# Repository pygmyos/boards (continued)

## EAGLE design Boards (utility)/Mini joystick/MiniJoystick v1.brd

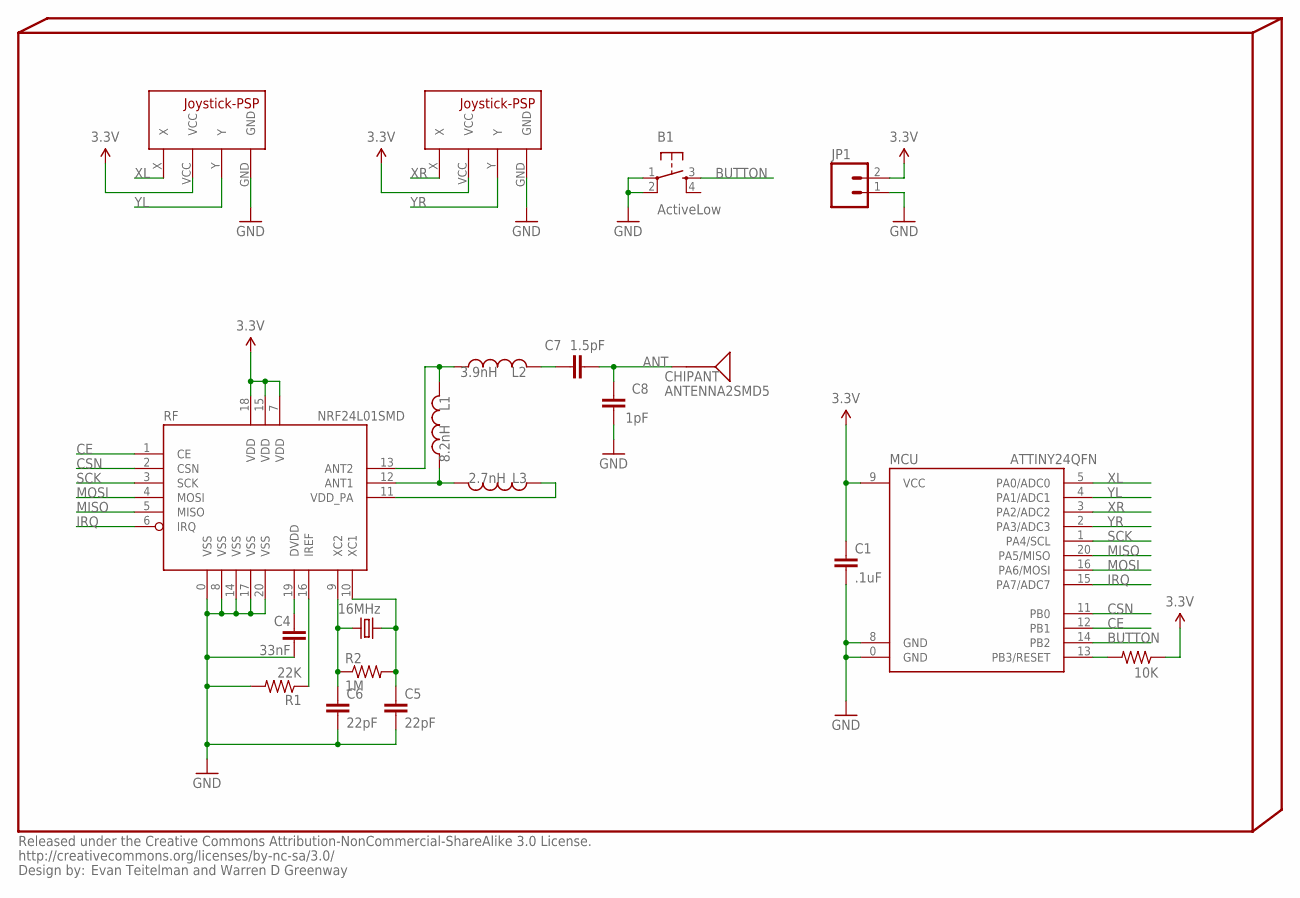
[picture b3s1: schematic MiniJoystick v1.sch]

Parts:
B1: ActiveLow; TACTILE_SWITCH_SMD
C1: .1uF; 0402-CAP
C4: 33nF; 0402-CAP
C5, C6: 22pF; 0402-CAP
C7: 1.5pF; 0402-CAP
C8: 1pF; 0402-CAP
CHIPANT: ANTENNA2SMD5; ANTENNA-CHIP5
INFO4: Evan Teitelman and Warren D Greenway; %CC-NC-SA
JOYSTICK_LEFT: JOYSTICK-PSP1000NOHOLES; JOYSTICK-PSP1000NH_
JOYSTICK_RIGHT: JOYSTICK-PSP1000NOHOLES; JOYSTICK-PSP1000NH_
JP1: M02-JST-2MM-SMT; JST-2-SMD
L1: 8.2nH; C0402
L2: 3.9nH; C0402
L3: 2.7nH; C0402
MCU: ATTINY24QFN; QFN20
R1: 22K; 0603-RES
R2: 1M; 0603-RES
R3: 10K; 0402-RES
RF: NRF24L01SMD; QFN20
Y1: 16MHz; CRYSTAL-SMD-5X3

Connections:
3.3V: C1.1, JOYSTICK_LEFT.VCC, JOYSTICK_RIGHT.VCC, JP1.2, MCU.9 (VCC), R3.1, RF.7 (VDD), RF.15 (VDD), RF.18 (VDD)
ANT: C7.2, C8.2, CHIPANT.FEED
ANT1: L1.1, L3.2, RF.12 (ANT1)
ANT2: L1.2, L2.1, RF.13 (ANT2)
BUTTON: B1.3, MCU.14 (PB2)
CE: MCU.12 (PB1), RF.1 (CE)
CSN: MCU.11 (PB0), RF.2 (CSN)
DVDD: C4.1, RF.19 (DVDD)
GND: B1.1, B1.2, C1.2, C4.2, C5.2, C6.2, C8.1, JOYSTICK_LEFT.GND, JOYSTICK_RIGHT.GND, JP1.1, MCU.0 (GND), MCU.8 (GND), R1.2, RF.0 (VSS), RF.8 (VSS), RF.14 (VSS), RF.17 (VSS), RF.20 (VSS)
IREF: R1.1, RF.16 (IREF)
IRQ: MCU.15 (PA7/ADC7), RF.6 (IRQ)
MISO: MCU.20 (PA5/MISO), RF.5 (MISO)
MOSI: MCU.16 (PA6/MOSI), RF.4 (MOSI)
unnamed: C7.1, L2.2
RESET: MCU.13 (PB3/RESET), R3.2
SCK: MCU.1 (PA4/SCL), RF.3 (SCK)
VDD_PA: L3.1, RF.11 (VDD_PA)
XC1: C5.1, R2.2, RF.10 (XC1), Y1.3 (2)
XC2: C6.1, R2.1, RF.9 (XC2), Y1.1
XL: JOYSTICK_LEFT.X, MCU.5 (PA0/ADC0)
XR: JOYSTICK_RIGHT.X, MCU.3 (PA2/ADC2)
YL: JOYSTICK_LEFT.Y, MCU.4 (PA1/ADC1)
YR: JOYSTICK_RIGHT.Y, MCU.2 (PA3/ADC3)

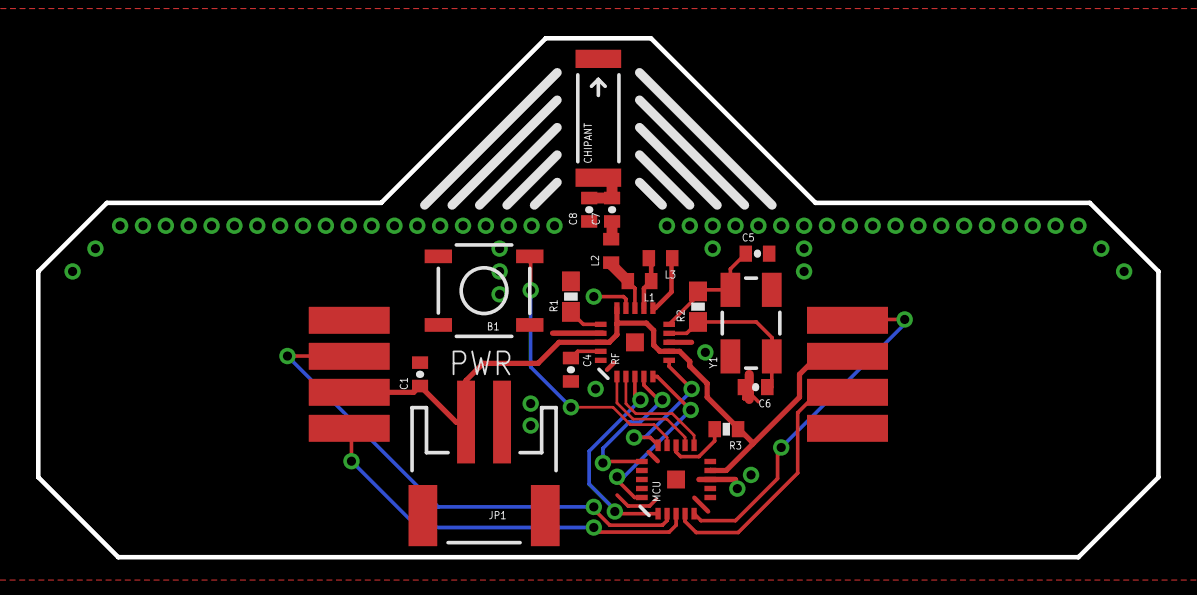
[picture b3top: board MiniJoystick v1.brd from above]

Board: 2 copper layers, 62.2 x 28.8 mm, 21 parts (0 on the bottom side), 23 nets.

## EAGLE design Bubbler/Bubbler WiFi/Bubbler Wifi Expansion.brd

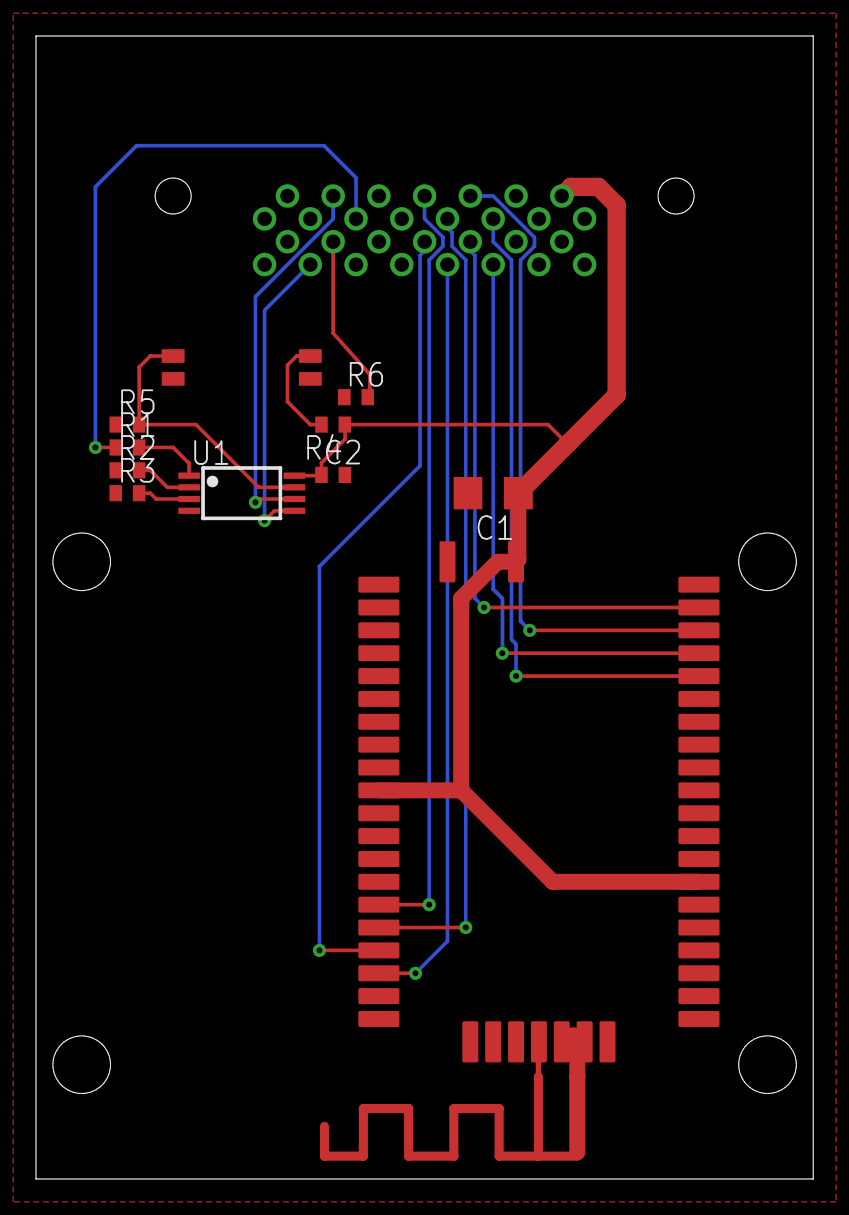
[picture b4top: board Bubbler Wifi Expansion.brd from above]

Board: 2 copper layers, 43.2 x 63.5 mm, 13 parts (0 on the bottom side), 20 nets.

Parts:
C1: C1206
C2: C0402
R1, R2, R3, R4, R5: R0402
R6: 47K; R0402
U1: EEPROM-ST-M24C64; TSSOP8
U2: WIFI-RN-171
U$1: SWITCH-DIP-GDH-02
U$2: BUBBLER_CARD; CONNECTOR-JAE-TX24-30M
U$3: ANTENNA-RN-171; RN-171-ANTENNA

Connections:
3.3V: C1.1, C2.1, R4.1, U1.8, U2.P10, U2.P34, U2.P49, U$2.P4
CARD_ID: R1.1, U$2.P22
CARD_SCL: U1.6, U$2.P24
CARD_SDA: U1.5, U$2.P25
CTS: U2.P44, U$2.P9
GND: C1.2, C2.2, R2.1, R3.1, R5.1, R6.1, U1.4, U2.P1, U2.P14, U2.P20, U2.P21, U2.P22, U2.P23, U2.P25, U2.P26, U2.P27, U2.P28, U2.P39, U2.P47, U$2.P5, U$2.P26, U$2.P28, U$2.P30, U$3.GND
unnamed: R3.2, U1.3
unnamed: R2.2, U1.2
unnamed: R1.2, U1.1
unnamed: R5.2, U1.7, U$1.P1
unnamed: R6.2, U$2.P23
unnamed: R4.2, U$1.P4
unnamed: U2.P24, U$3.ANTENNA
RTS: U2.P43, U$2.P10
RX: U2.P45, U$2.P12
TX: U2.P46, U$2.P11
WIFI_CS: U2.P18, U$2.P13
WIFI_MISO: U2.P17, U$2.P15
WIFI_MOSI: U2.P15, U$2.P16
WIFI_SCK: U2.P16, U$2.P14
